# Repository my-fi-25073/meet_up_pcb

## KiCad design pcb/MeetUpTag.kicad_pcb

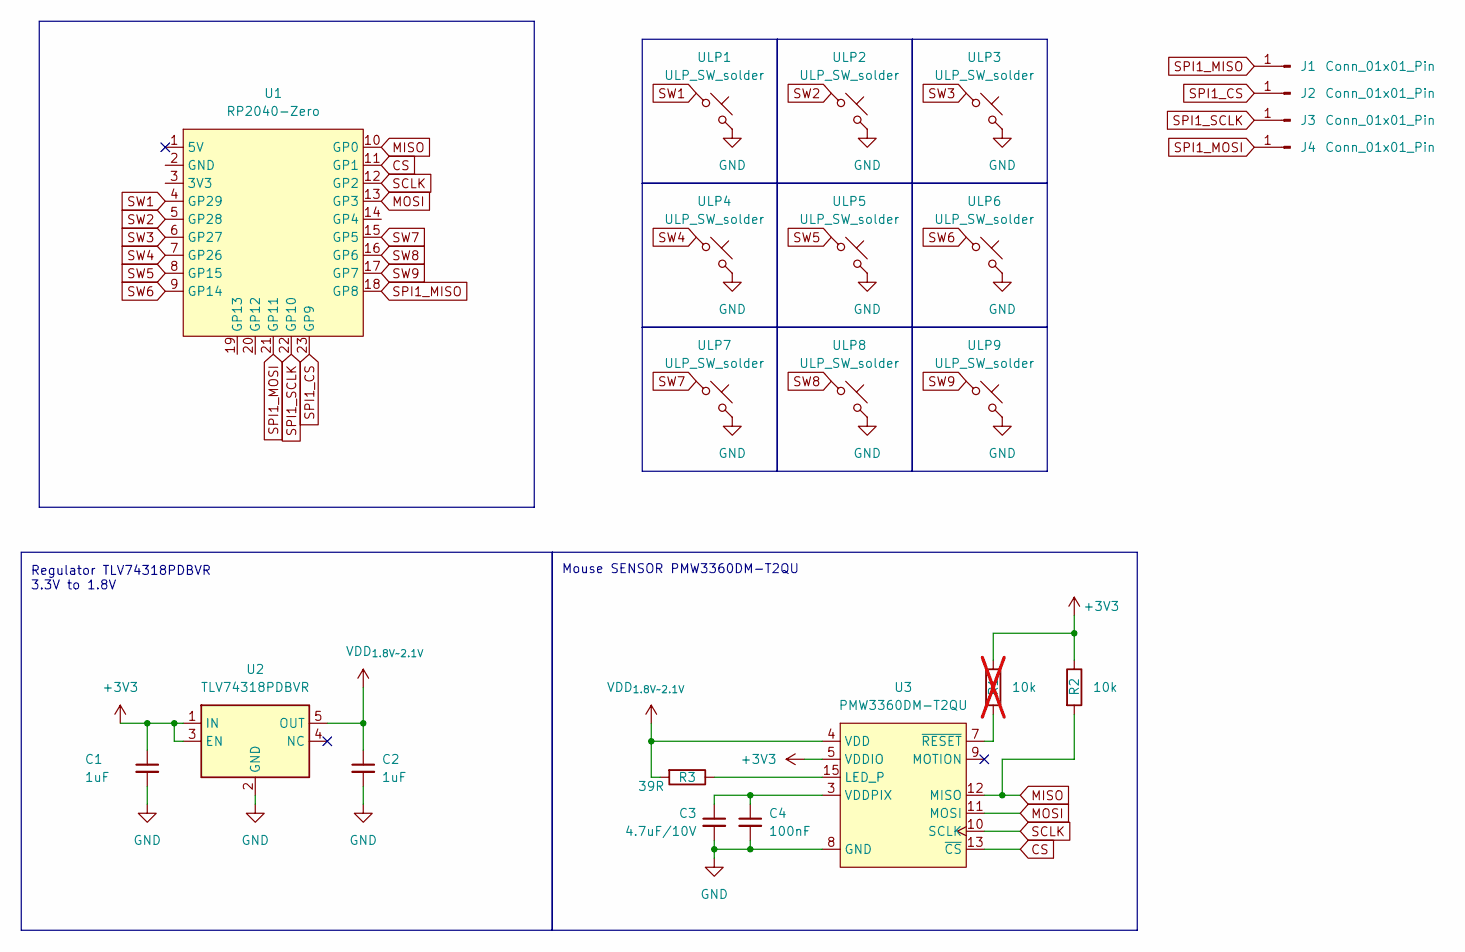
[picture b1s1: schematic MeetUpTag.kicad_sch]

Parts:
C1, C2: 1uF; C_0402_1005Metric
C3: 4.7uF/10V; C_0402_1005Metric
C4: 100nF; C_0402_1005Metric
J1, J2, J3, J4: Conn_01x01_Pin; TestPoint_THTPad_D1.5mm_Drill0.7mm
R1: 10k; R_0805_2012Metric_Pad1.20x1.40mm_HandSolder; not fitted
R2: 10k; R_0402_1005Metric
R3: 39R; R_0402_1005Metric
U1: RP2040-Zero; RP2040 Zero
U2: TLV74318PDBVR; SOT-23-5; MPN C485152
U3: PMW3360DM-T2QU; PMW3360DM-T2QU 16Pin
ULP1, ULP2, ULP3, ULP4, ULP5, ULP6, ULP7, ULP8, ULP9: ULP_SW_solder; SW_MX_ULP_1u

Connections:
+3V3: C1.1, R1.1, R2.1, U2.1 (IN), U2.3 (EN), U3.5 (VDDIO)
CS: U1.11 (GP1), U3.13 (~CS)
GND: C1.2, C2.2, C3.2, C4.2, U2.2 (GND), U3.8 (GND), ULP1.2, ULP2.2, ULP3.2, ULP4.2, ULP5.2, ULP6.2, ULP7.2, ULP8.2, ULP9.2
MISO: R2.2, U1.10 (GP0), U3.12 (MISO)
MOSI: U1.13 (GP3), U3.11 (MOSI)
unnamed: R3.1, U3.15 (LED_P)
unnamed: C3.1, C4.1, U3.3 (VDDPIX)
unnamed: R1.2, U3.7 (~RESET)
SCLK: U1.12 (GP2), U3.10 (SCLK)
SPI1_CS: J2.1, U1.23 (GP9)
SPI1_MISO: J1.1, U1.18 (GP8)
SPI1_MOSI: J4.1, U1.21 (GP11)
SPI1_SCLK: J3.1, U1.22 (GP10)
SW1: U1.4 (GP29), ULP1.1
SW2: U1.5 (GP28), ULP2.1
SW3: U1.6 (GP27), ULP3.1
SW4: U1.7 (GP26), ULP4.1
SW5: U1.8 (GP15), ULP5.1
SW6: U1.9 (GP14), ULP6.1
SW7: U1.15 (GP5), ULP7.1
SW8: U1.16 (GP6), ULP8.1
SW9: U1.17 (GP7), ULP9.1
VDD_{1.8V~2.1V}: C2.1, R3.2, U2.5 (OUT), U3.4 (VDD)

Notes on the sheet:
Regulator TLV74318PDBVR 3.3V to 1.8V
Mouse SENSOR PMW3360DM-T2QU

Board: 2 copper layers, 23 parts (0 on the bottom side), 23 nets, no tracks yet.

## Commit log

2025-05-08 Added MeetUpTag PCB files.
2025-05-08 added symbol and footprint
